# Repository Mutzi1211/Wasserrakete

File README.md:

# 🚀 Projektstruktur: Wasserrakete

Ein Überblick über alle Projektbestandteile – von CAD über Code bis zu Anforderungen und Abgaben.

---

### 📁 Abgabe/Poster
- 📄 **Projekt 2 Plakatvorstellung A2.pdf**  
  ➤ Das Poster für die offizielle Projektpräsentation.
---

### 📁 cad
3D-Modelle und technische Zeichnungen zur Rakete.

- 📁 **Rakete**  
 ➤ Enthält die CAD-Dateien des Raketenmodells  
  ➤ Dient zur Fertigung 

- 📄 **Rakete.pdf**  
  ➤ Zeichnung für die Rakete
---

### 📁 code
Die komplette Firmware für den Datenlogger (ESP32, SD-Logging, Webserver etc.)

---

### 📁 pcb
Alle Dateien zur Platine für den Datenlogger.

- 📁 **data_logger**  
  ➤ PCB-Design, dass alles auf einer Platine ist. Leider nicht mehr fertig geworden, aber wichtig für die Reproduktion

- 📁 **Prototyp**  
  ➤ Aktuelle Stand. Zusammengesteckt aus verschiedenen Bauteilen und auf einem 3D-Druck Boden montiert.

  - 📄 **Schaltplan.pdf**  
  ➤ Aktueller Schaltplan 

- 📄 **PCB.pdf**  
  ➤ Visualisierung der geplanten PCBs. 

- 📄 **Schematic.pdf**  
 ➤ Schematic des geplanten PCBs.

---

### 📁 Requirement Engineering
Projektplanung, Funktionsdefinitionen und Anforderungen.

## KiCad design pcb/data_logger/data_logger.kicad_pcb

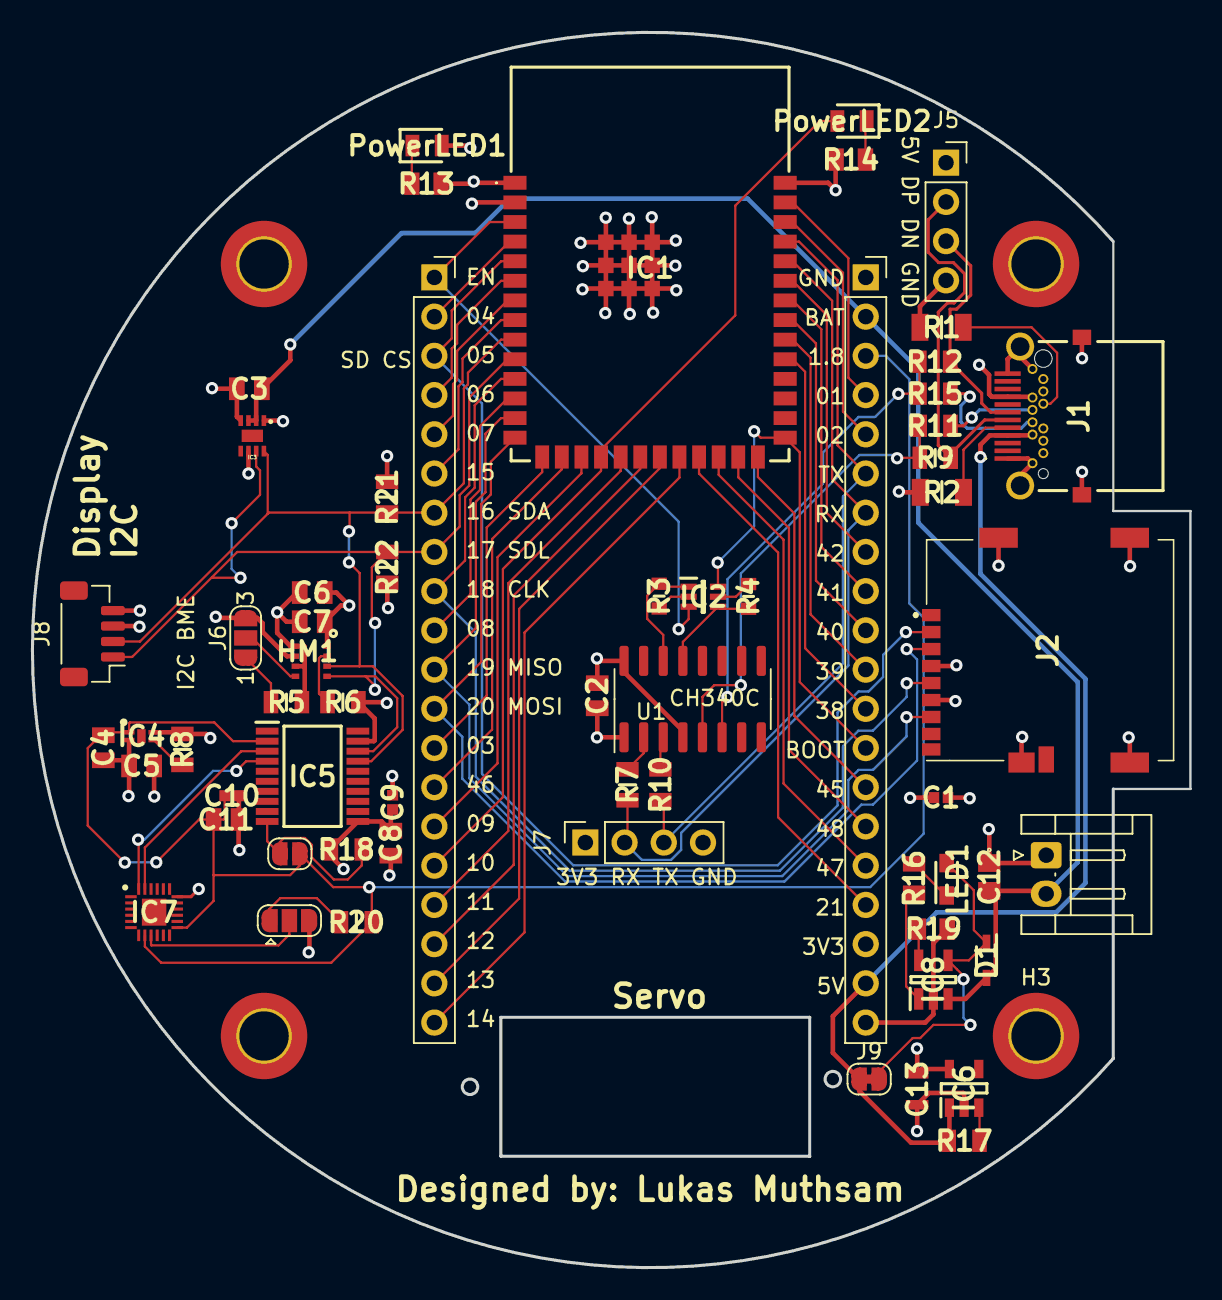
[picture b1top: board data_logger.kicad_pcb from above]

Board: 4 copper layers, 75.0 x 80.0 mm, 65 parts (0 on the bottom side), 69 nets.

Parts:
C1: 10uF; CAPC1005X70N
C2, C3: 08055C104KAT2A; CAPC2012X94N
C4, C5: 1uF; CAPC2012X140N
C6, C7: 0.1uF; CAPC2012X94N
C8, C11: 01.uF; CAPC2012X94N
C9, C10: C10uF; CAPC1005X70N
C12: C4.7uF; C0805
C13: C2.2uF; CAPC2012X145N
D1: 3A-10V-280mV; SOD2513X110N
H1, H2, H3, H4: MountingHole_Pad; MountingHole_3.2mm_M3_DIN965_Pad_TopBottom
HM1: BME280
IC1: ESP32-S3-WROOM-2-N32R8V; ESP32S3WROOM2N32R8V
IC2: MBT3904DW1T1G; SOT65P210X110-6N
IC3: MAX17048G+T10; DFN-8
IC4: MIC94310-GYMT-TR; SON50P155X120X60-5N-D
IC5: TXS0108EQPWRQ1; SOP65P640X120-20N
IC6: AP2112K-3.3TRG1; SOT95P282X130-5N
IC7: ICM-20948; QFN40P300X300X105-25N-D
IC8: MCP73831T-2ACI_OT; SOT95P270X145-5N
J1: UJ32-C-H-G-H2-SMT-TR; UJ32CHGH2SMTTR
J2: 045138008100858+; 045138008100858
J3, J4: Conn_01x20_Pin; PinSocket_1x20_P2.54mm_Vertical
J5, J7: Conn_01x04; PinSocket_1x04_P2.54mm_Vertical
J6: Conn_01x03_Pin; SolderJumper-3_P1.3mm_Open_RoundedPad1.0x1.5mm_NumberLabels
J8: Conn_01x04; JST_SH_BM04B-SRSS-TB_1x04-1MP_P1.00mm_Vertical
J9: LiPo; SolderJumper-2_P1.3mm_Bridged_RoundedPad1.0x1.5mm
J10: TXS0108E; SolderJumper-2_P1.3mm_Open_RoundedPad1.0x1.5mm
J11: 1769; JST_EH_S2B-EH_1x02_P2.50mm_Horizontal
J12: SolderJumper-3_P1.3mm_Open_RoundedPad1.0x1.5mm
LED1: VLMY234ABCA-GS08; LEDM2214X140N
PowerLED1, PowerLED2: 150080RS75000; LEDC2012X80N
R1, R2: 5.1k; RESC3116X65N
R3, R4: 10k; RESC1608X55N
R5, R6, R8, R20, R21, R22: R4.7k; RESC2012X50N
R7, R9, R10, R11, R12, R15: R0; RESC2013X84N
R13, R14, R16: MCU0805MD1000BP100; RESC2012X55N
R17, R18: 330k; RESC2012X50N
R19: R2.2k; RESC2013X65N
U1: CH340C; SOIC-16_3.9x9.9mm_P1.27mm

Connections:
+1V8: C4.2, C10.2, C11.2, IC4.1 (VOUT), IC5.2 (VCCA), IC7.8 (VDDIO), IC7.13 (VDD), J4.3, J10.1, R20.2
+3V3: C1.2, C2.2, C5.2, C6.2, C7.2, C8.2, C9.2, C13.2, HM1.6 (VDDIO), HM1.8 (VDD), IC1.2 (3V3), IC4.4 (VIN), IC5.19 (VCCB), IC6.5 (VOUT), J2.4 (VDD), J4.18, J7.1, J8.3, PowerLED1.2 (A), R5.2, R6.2, R8.2, R21.2, R22.2, U1.4 (V3), U1.16 (VCC)
+3V8: C3.2, C12.2, D1.2 (A), IC3.2 (CELL), IC3.3 (VDD), IC8.3 (VBAT), J4.2, J11.2
+5V: IC6.1 (VIN), J1.A4 (VBUS_1), J1.A9 (VBUS_2), J1.B4 (VBUS_3), J1.B9 (VBUS_4), J4.19, J5.1, J9.1, R17.2
/CH340_DTR: IC2.4 (E_1), R4.2, U1.13 (~DTR)
/CH340_RTS: IC2.1 (E_2), R3.1, U1.14 (~RTS)
/CHIP_BOOT: IC1.27 (IO0), IC2.6 (C_2), J4.13
/CHIP_RX: IC1.36 (RXD0), J4.7, J7.2, R7.2
/CHIP_TX: IC1.37 (TXD0), J4.6, J7.3, R10.2
/Chip_EN: IC1.3 (EN), IC2.3 (C_1), J3.1
/DN1: J1.A7 (DN1), J5.3, R12.1
/DN2: J1.B7 (DN2), R15.1
/DP1: J1.A6 (DP1), J5.2, R9.1
/DP2: J1.B6 (DP2), R11.1
/GPIO1: IC1.39 (IO1), J4.4
/GPIO2: IC1.38 (IO2), J4.5
/GPIO3: IC1.15 (IO3), J3.13
/GPIO4: IC1.4 (IO4), J3.2
/GPIO5_CS: IC1.5 (IO5), J2.2 (CD/DAT3), J3.3
/GPIO6: IC1.6 (IO6), J3.4
/GPIO7: IC1.7 (IO7), J3.5
/GPIO8: IC1.12 (IO8), J3.10
/GPIO9: IC1.17 (IO9), J3.15
/GPIO10: IC1.18 (IO10), J3.16, PowerLED2.2 (A)
/GPIO11: IC1.19 (IO11), J3.17
/GPIO12: IC1.20 (IO12), J3.18
/GPIO13: IC1.21 (IO13), J3.19
/GPIO14: IC1.22 (IO14), J3.20
/GPIO15: IC1.8 (IO15), J3.6
/GPIO18_CLK: IC1.11 (IO18), J2.5 (CLK), J3.9
/GPIO19_MISO: IC1.13 (IO19), J2.7 (DAT0), J3.11
/GPIO20_MOSI: IC1.14 (IO20), J2.3 (CMD), J3.12
/GPIO21: IC1.23 (IO21), J4.17
/GPIO38: IC1.31 (IO38), J4.12
/GPIO39: IC1.32 (IO39), J4.11
/GPIO40: IC1.33 (IO40), J4.10
/GPIO41: IC1.34 (IO41), J4.9
/GPIO42: IC1.35 (IO42), J4.8
/GPIO45: IC1.26 (IO45), J4.14
/GPIO46: IC1.16 (IO46), J3.14
/GPIO47: IC1.24 (IO47), J4.16
/GPIO48: IC1.25 (IO48), J4.15
/SCL: HM1.4 (SCK), IC1.10 (IO17), IC3.7 (SCL), IC5.18 (B2), J3.8, J8.1, R22.1
/SCL_low: IC5.3 (A2), IC7.23 (SCL_/_SCLK)
/SDA: HM1.3 (SDI), IC1.9 (IO16), IC3.8 (SDA), IC5.17 (B3), J3.7, J8.2, R21.1
/SDA_low: IC5.4 (A3), IC7.24 (SDA_/_SDI)
GND: C1.1, C2.1, C3.1, C4.1, C5.1, C6.1, C7.1, C8.1, C9.1, C10.1, C11.1, C12.1, C13.1, H1.1, H2.1, H3.1, H4.1, HM1.1 (GND_1), HM1.7 (GND_2), IC1.1 (GND_1), IC1.40 (GND_2), IC1.41 (GND_3), IC1.42 (GND_4), IC1.43 (GND_5), IC1.44 (GND_6), IC1.45 (GND_7), IC1.46 (GND_8), IC1.47 (GND_9), IC1.48 (GND_10), IC1.49 (GND_11), IC3.1 (CTG), IC3.4 (GND), IC3.6 (QSTRT), IC4.2 (GND), IC5.11 (GND), IC6.2 (GND), IC7.18 (GND), IC8.2 (VSS), J1.A1 (GND_1), J1.A12 (GND_2), J1.B1 (GND_3), J1.B12 (GND_4), J1.MH1, J1.MH2, J1.MP1, J1.MP2, J2.6 (VSS), J2.10, J2.11, J2.12, J2.13, J4.1, J4.20, J5.4, J6.3, J7.4, J8.4, J11.1, J12.3, R1.1, R2.1, R13.2, R14.2, R18.1, R19.1, U1.1 (GND)
unnamed: D1.1 (K), IC8.4 (VDD), J9.2, LED1.2 (A)
unnamed: HM1.2 (CSB), R6.1
unnamed: HM1.5 (SDO), J6.2
unnamed: IC2.5 (B_1), R4.1
unnamed: IC2.2 (B_2), R3.2
unnamed: IC4.3 (EN), R8.1
unnamed: IC5.10 (OE), J10.2, R18.2
unnamed: IC6.3 (EN), R17.1
unnamed: IC7.9 (SDO_/_AD0), J12.2
unnamed: IC8.5 (PROG), R19.2
unnamed: IC8.1 (STAT), R16.2
unnamed: J1.A5 (CC1), R2.2
unnamed: J1.B5 (CC2), R1.2
unnamed: J6.1, R5.1
unnamed: J12.1, R20.1
unnamed: LED1.1 (K), R16.1
unnamed: PowerLED1.1 (K), R13.1
unnamed: PowerLED2.1 (K), R14.1
unnamed: R10.1, U1.3 (RXD)
unnamed: R7.1, U1.2 (TXD)
unnamed: R9.2, R11.2, U1.5 (UD+)
unnamed: R12.2, R15.2, U1.6 (UD-)

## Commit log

2025-06-15 start programm
2025-06-16 first try with webserver
2025-06-16 webserver aber lädt langsam
2025-06-16 BNO085
2025-06-16 BNO086 geht
2025-06-17 working BNO086
2025-06-17 .venv nicht hochladen
2025-06-17 adding bme280
2025-06-17 adding SD-Card
2025-06-18 geht alles hoffentlich
2025-06-20 kein ESP NOW aber Webserver clean
2025-06-20 Remove .venv from repo and add to .gitignore
2025-06-20 alles wieder auf einem stand
2025-06-24 alles geht soweit
2025-06-25 working battery
2025-06-27 geht alles soweit
2025-06-27 adding servo and oled
2025-06-27 bno086 mit adafruit
2025-06-27 ich geh ins bett
2025-07-12 last working
2025-07-12 aktueller stand
2025-07-13 halb umgesetzt
2025-07-13 alles sauber
2025-07-13 cad pdf
2025-07-13 code sortiert
2025-07-13 git ignore
2025-07-13 fix DS_store
2025-07-17 aktualisierung
